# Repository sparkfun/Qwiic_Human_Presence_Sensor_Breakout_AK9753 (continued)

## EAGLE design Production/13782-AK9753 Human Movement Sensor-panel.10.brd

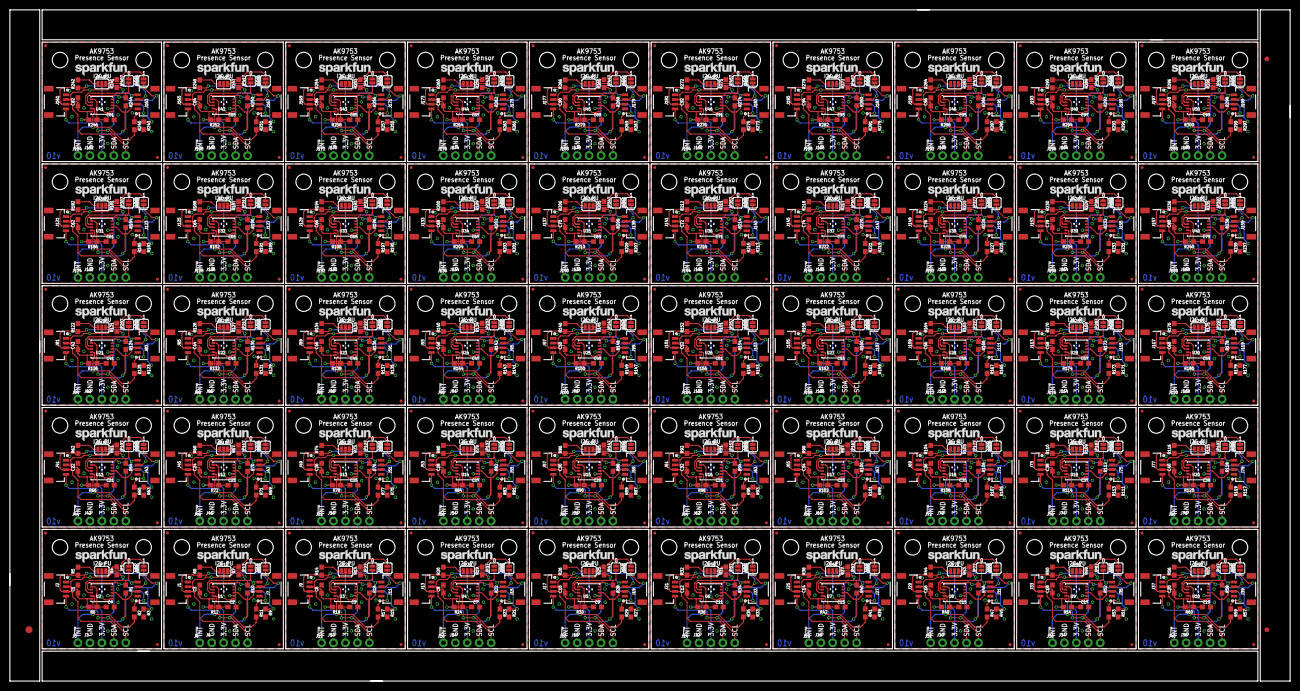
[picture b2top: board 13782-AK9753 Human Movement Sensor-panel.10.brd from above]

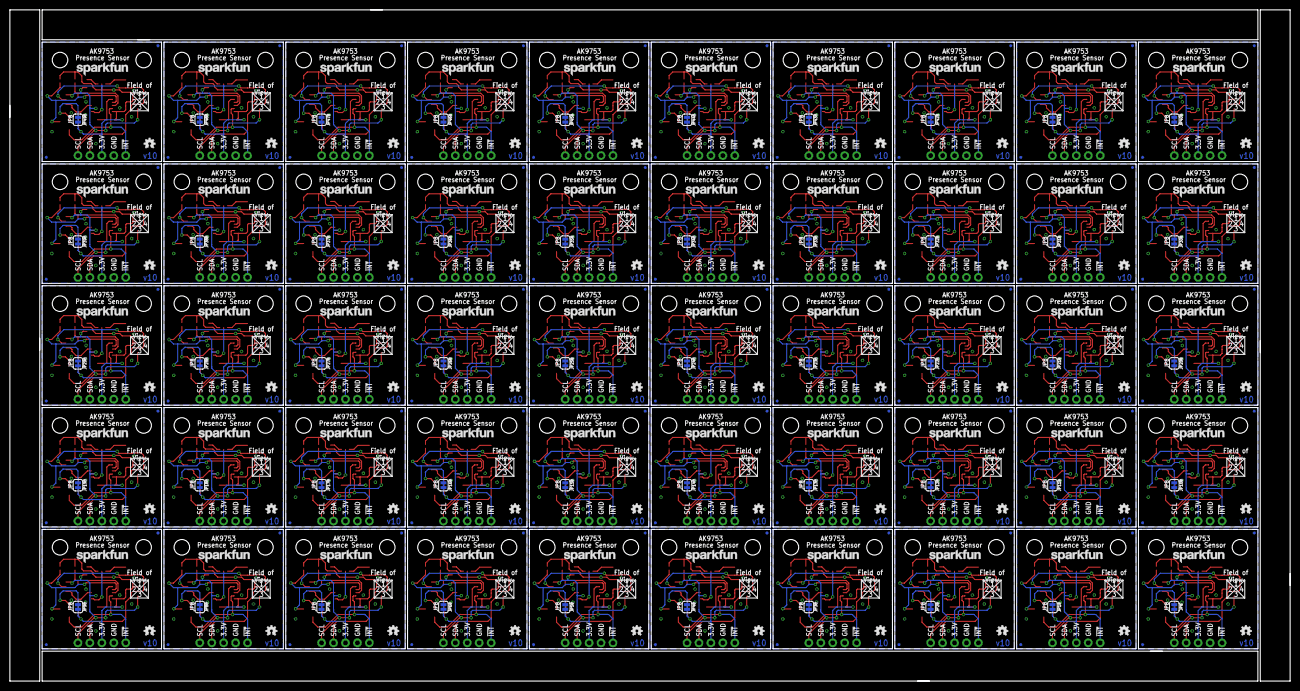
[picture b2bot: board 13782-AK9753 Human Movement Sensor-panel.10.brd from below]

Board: 2 copper layers, 272.3 x 142.7 mm, 1303 parts (250 on the bottom side), 550 nets.

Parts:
C1, C2, C3, C4, C5, C6, C7, C8, C9, C10, C11, C12, C13, C14, C15, C16, C17, C18, C19, C20, C21, C22, C23, C24, C25, C26, C27, C28, C29, C30, C31, C32, C33, C34, C35, C36, C37, C38, C39, C40, C41, C42, C43, C44, C45, C46, C47, C48, C49, C50, C51, C52, C53, C54, C55, C56, C57, C58, C59, C60, C61, C62, C63, C64, C65, C66, C67, C68, C69, C70, C71, C72, C73, C74, C75, C76, C77, C78, C79, C80, C81, C82, C83, C84, C85, C86, C87, C88, C89, C90, C91, C92, C93, C94, C95, C96, C97, C98, C99, C100: 1.0uF; 0603
E$1: FIDUCIAL-1.5X3
E$7, E$8: FIDUCIAL-1X2
J1, J2, J4, J7, J9, J11, J13, J15, J17, J19, J21, J23, J25, J27, J29, J31, J33, J35, J37, J39, J41, J43, J45, J47, J49, J51, J53, J55, J57, J59, J61, J63, J65, J67, J69, J71, J73, J75, J77, J79, J81, J83, J85, J87, J89, J91, J93, J95, J97, J99, J101, J103, J105, J107, J109, J111, J113, J115, J117, J119, J121, J123, J125, J127, J129, J131, J133, J135, J137, J139, J141, J143, J145, J147, J149, J151, J153, J155, J157, J159, J161, J163, J165, J167, J169, J171, J173, J175, J177, J179, J181, J183, J185, J187, J189, J191, J193, J195, J197, J199: 1X04_1MM_RA
J3, J6, J10, J14, J18, J22, J26, J30, J34, J38, J42, J46, J50, J54, J58, J62, J66, J70, J74, J78, J82, J86, J90, J94, J98, J102, J106, J110, J114, J118, J122, J126, J130, J134, J138, J142, J146, J150, J154, J158, J162, J166, J170, J174, J178, J182, J186, J190, J194, J198: PTH; 1X04_NO_SILK
J5, J8, J12, J16, J20, J24, J28, J32, J36, J40, J44, J48, J52, J56, J60, J64, J68, J72, J76, J80, J84, J88, J92, J96, J100, J104, J108, J112, J116, J120, J124, J128, J132, J136, J140, J144, J148, J152, J156, J160, J164, J168, J172, J176, J180, J184, J188, J192, J196, J200: 1X01_NO_SILK
JP1, JP5, JP16, JP17, JP26, JP27, JP36, JP37, JP46, JP47, JP56, JP57, JP66, JP67, JP76, JP77, JP86, JP87, JP96, JP97, JP106, JP107, JP116, JP117, JP126, JP127, JP136, JP137, JP146, JP147, JP156, JP157, JP166, JP167, JP176, JP177, JP186, JP187, JP196, JP197, JP206, JP207, JP216, JP217, JP226, JP227, JP236, JP237, JP246, JP247, JP256, JP257, JP266, JP267, JP276, JP277, JP286, JP287, JP296, JP297, JP306, JP307, JP316, JP317, JP326, JP327, JP336, JP337, JP346, JP347, JP356, JP357, JP366, JP367, JP376, JP377, JP386, JP387, JP396, JP397, JP406, JP407, JP416, JP417, JP426, JP427, JP436, JP437, JP446, JP447, JP456, JP457, JP466, JP467, JP476, JP477, JP486, JP487, JP496, JP497: SMT-JUMPER_2_NO_SILK
JP2, JP6, JP9, JP10, JP13, JP14, JP19, JP20, JP23, JP24, JP29, JP30, JP33, JP34, JP39, JP40, JP43, JP44, JP49, JP50, JP53, JP54, JP59, JP60, JP63, JP64, JP69, JP70, JP73, JP74, JP79, JP80, JP83, JP84, JP89, JP90, JP93, JP94, JP99, JP100, JP103, JP104, JP109, JP110, JP113, JP114, JP119, JP120, JP123, JP124, JP129, JP130, JP133, JP134, JP139, JP140, JP143, JP144, JP149, JP150, JP153, JP154, JP159, JP160, JP163, JP164, JP169, JP170, JP173, JP174, JP179, JP180, JP183, JP184, JP189, JP190, JP193, JP194, JP199, JP200, JP203, JP204, JP209, JP210, JP213, JP214, JP219, JP220, JP223, JP224, JP229, JP230, JP233, JP234, JP239, JP240, JP243, JP244, JP249, JP250, JP253, JP254, JP259, JP260, JP263, JP264, JP269, JP270, JP273, JP274, JP279, JP280, JP283, JP284, JP289, JP290, JP293, JP294, JP299, JP300, JP303, JP304, JP309, JP310, JP313, JP314, JP319, JP320, JP323, JP324, JP329, JP330, JP333, JP334, JP339, JP340, JP343, JP344, JP349, JP350, JP353, JP354, JP359, JP360, JP363, JP364, JP369, JP370, JP373, JP374, JP379, JP380, JP383, JP384, JP389, JP390, JP393, JP394, JP399, JP400, JP403, JP404, JP409, JP410, JP413, JP414, JP419, JP420, JP423, JP424, JP429, JP430, JP433, JP434, JP439, JP440, JP443, JP444, JP449, JP450, JP453, JP454, JP459, JP460, JP463, JP464, JP469, JP470, JP473, JP474, JP479, JP480, JP483, JP484, JP489, JP490, JP493, JP494, JP499, JP500: FIDUCIALUFIDUCIAL; MICRO-FIDUCIAL
JP3, JP4, JP11, JP12, JP21, JP22, JP31, JP32, JP41, JP42, JP51, JP52, JP61, JP62, JP71, JP72, JP81, JP82, JP91, JP92, JP101, JP102, JP111, JP112, JP121, JP122, JP131, JP132, JP141, JP142, JP151, JP152, JP161, JP162, JP171, JP172, JP181, JP182, JP191, JP192, JP201, JP202, JP211, JP212, JP221, JP222, JP231, JP232, JP241, JP242, JP251, JP252, JP261, JP262, JP271, JP272, JP281, JP282, JP291, JP292, JP301, JP302, JP311, JP312, JP321, JP322, JP331, JP332, JP341, JP342, JP351, JP352, JP361, JP362, JP371, JP372, JP381, JP382, JP391, JP392, JP401, JP402, JP411, JP412, JP421, JP422, JP431, JP432, JP441, JP442, JP451, JP452, JP461, JP462, JP471, JP472, JP481, JP482, JP491, JP492: STAND-OFF
JP7, JP15, JP25, JP35, JP45, JP55, JP65, JP75, JP85, JP95, JP105, JP115, JP125, JP135, JP145, JP155, JP165, JP175, JP185, JP195, JP205, JP215, JP225, JP235, JP245, JP255, JP265, JP275, JP285, JP295, JP305, JP315, JP325, JP335, JP345, JP355, JP365, JP375, JP385, JP395, JP405, JP415, JP425, JP435, JP445, JP455, JP465, JP475, JP485, JP495: SMT-JUMPER_3_2-NC_PASTE_SILK
JP8, JP18, JP28, JP38, JP48, JP58, JP68, JP78, JP88, JP98, JP108, JP118, JP128, JP138, JP148, JP158, JP168, JP178, JP188, JP198, JP208, JP218, JP228, JP238, JP248, JP258, JP268, JP278, JP288, JP298, JP308, JP318, JP328, JP338, JP348, JP358, JP368, JP378, JP388, JP398, JP408, JP418, JP428, JP438, JP448, JP458, JP468, JP478, JP488, JP498: SMT-JUMPER_2_NC_TRACE_SILK
LOGO1, LOGO3, LOGO5, LOGO7, LOGO9, LOGO11, LOGO13, LOGO15, LOGO17, LOGO19, LOGO21, LOGO23, LOGO25, LOGO27, LOGO29, LOGO31, LOGO33, LOGO35, LOGO37, LOGO39, LOGO41, LOGO43, LOGO45, LOGO47, LOGO49, LOGO51, LOGO53, LOGO55, LOGO57, LOGO59, LOGO61, LOGO63, LOGO65, LOGO67, LOGO69, LOGO71, LOGO73, LOGO75, LOGO77, LOGO79, LOGO81, LOGO83, LOGO85, LOGO87, LOGO89, LOGO91, LOGO93, LOGO95, LOGO97, LOGO99: OSHW-LOGOMINI; OSHW-LOGO-MINI
LOGO2, LOGO4, LOGO6, LOGO8, LOGO10, LOGO12, LOGO14, LOGO16, LOGO18, LOGO20, LOGO22, LOGO24, LOGO26, LOGO28, LOGO30, LOGO32, LOGO34, LOGO36, LOGO38, LOGO40, LOGO42, LOGO44, LOGO46, LOGO48, LOGO50, LOGO52, LOGO54, LOGO56, LOGO58, LOGO60, LOGO62, LOGO64, LOGO66, LOGO68, LOGO70, LOGO72, LOGO74, LOGO76, LOGO78, LOGO80, LOGO82, LOGO84, LOGO86, LOGO88, LOGO90, LOGO92, LOGO94, LOGO96, LOGO98, LOGO100: SFE_LOGO_NAME.1_INCH; SFE_LOGO_NAME_.1
R1, R2, R3, R9, R10, R11, R15, R16, R17, R21, R22, R23, R27, R28, R29, R33, R34, R35, R39, R40, R41, R45, R46, R47, R51, R52, R53, R57, R58, R59, R63, R64, R65, R69, R70, R71, R75, R76, R77, R81, R82, R83, R87, R88, R89, R93, R94, R95, R99, R100, R101, R105, R106, R107, R111, R112, R113, R117, R118, R119, R123, R124, R125, R129, R130, R131, R135, R136, R137, R141, R142, R143, R147, R148, R149, R153, R154, R155, R159, R160, R161, R165, R166, R167, R171, R172, R173, R177, R178, R179, R183, R184, R185, R189, R190, R191, R195, R196, R197, R201, R202, R203, R207, R208, R209, R213, R214, R215, R219, R220, R221, R225, R226, R227, R231, R232, R233, R237, R238, R239, R243, R244, R245, R249, R250, R251, R255, R256, R257, R261, R262, R263, R267, R268, R269, R273, R274, R275, R279, R280, R281, R285, R286, R287, R291, R292, R293, R297, R298, R299: 10k; 0603
R4, R5, R7, R8, R13, R14, R19, R20, R25, R26, R31, R32, R37, R38, R43, R44, R49, R50, R55, R56, R61, R62, R67, R68, R73, R74, R79, R80, R85, R86, R91, R92, R97, R98, R103, R104, R109, R110, R115, R116, R121, R122, R127, R128, R133, R134, R139, R140, R145, R146, R151, R152, R157, R158, R163, R164, R169, R170, R175, R176, R181, R182, R187, R188, R193, R194, R199, R200, R205, R206, R211, R212, R217, R218, R223, R224, R229, R230, R235, R236, R241, R242, R247, R248, R253, R254, R259, R260, R265, R266, R271, R272, R277, R278, R283, R284, R289, R290, R295, R296: 4.7k; 0603
R6, R12, R18, R24, R30, R36, R42, R48, R54, R60, R66, R72, R78, R84, R90, R96, R102, R108, R114, R120, R126, R132, R138, R144, R150, R156, R162, R168, R174, R180, R186, R192, R198, R204, R210, R216, R222, R228, R234, R240, R246, R252, R258, R264, R270, R276, R282, R288, R294, R300: 330; 0603
U1, U2, U3, U4, U5, U6, U7, U8, U9, U10, U11, U12, U13, U14, U15, U16, U17, U18, U19, U20, U21, U22, U23, U24, U25, U26, U27, U28, U29, U30, U31, U32, U33, U34, U35, U36, U37, U38, U39, U40, U41, U42, U43, U44, U45, U46, U47, U48, U49, U50: AK9753; SON10
U$1, U$2, U$3, U$4, U$5, U$6, U$7, U$8, U$9, U$10, U$11, U$12, U$13, U$14, U$15, U$16, U$17, U$18, U$19, U$20, U$21, U$22, U$23, U$24, U$25, U$26, U$27, U$28, U$29, U$30, U$31, U$32, U$33, U$34, U$35, U$36, U$37, U$38, U$39, U$40, U$41, U$42, U$43, U$44, U$45, U$46, U$47, U$48, U$49, U$50: SFE_LOGO_NAME_.1

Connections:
3.3V: C1.1, J2.2, J3.2, J4.2, JP1.2, JP5.2, JP7.2, JP8.2, R6.2, U2.3, U2.6
3.3V1: C3.1, J1.2, J6.2, J7.2, JP15.2, JP16.2, JP17.2, JP18.2, R12.2, U1.3, U1.6
3.3V2: C6.1, J9.2, J10.2, J11.2, JP25.2, JP26.2, JP27.2, JP28.2, R18.2, U3.3, U3.6
3.3V3: C8.1, J13.2, J14.2, J15.2, JP35.2, JP36.2, JP37.2, JP38.2, R24.2, U4.3, U4.6
3.3V4: C10.1, J17.2, J18.2, J19.2, JP45.2, JP46.2, JP47.2, JP48.2, R30.2, U5.3, U5.6
3.3V5: C12.1, J21.2, J22.2, J23.2, JP55.2, JP56.2, JP57.2, JP58.2, R36.2, U6.3, U6.6
3.3V6: C14.1, J25.2, J26.2, J27.2, JP65.2, JP66.2, JP67.2, JP68.2, R42.2, U7.3, U7.6
3.3V7: C16.1, J29.2, J30.2, J31.2, JP75.2, JP76.2, JP77.2, JP78.2, R48.2, U8.3, U8.6
3.3V8: C18.1, J33.2, J34.2, J35.2, JP85.2, JP86.2, JP87.2, JP88.2, R54.2, U9.3, U9.6
3.3V9: C20.1, J37.2, J38.2, J39.2, JP95.2, JP96.2, JP97.2, JP98.2, R60.2, U10.3, U10.6
3.3V10: C22.1, J41.2, J42.2, J43.2, JP105.2, JP106.2, JP107.2, JP108.2, R66.2, U11.3, U11.6
3.3V11: C24.1, J45.2, J46.2, J47.2, JP115.2, JP116.2, JP117.2, JP118.2, R72.2, U12.3, U12.6
3.3V12: C26.1, J49.2, J50.2, J51.2, JP125.2, JP126.2, JP127.2, JP128.2, R78.2, U13.3, U13.6
3.3V13: C28.1, J53.2, J54.2, J55.2, JP135.2, JP136.2, JP137.2, JP138.2, R84.2, U14.3, U14.6
3.3V14: C30.1, J57.2, J58.2, J59.2, JP145.2, JP146.2, JP147.2, JP148.2, R90.2, U15.3, U15.6
3.3V15: C32.1, J61.2, J62.2, J63.2, JP155.2, JP156.2, JP157.2, JP158.2, R96.2, U16.3, U16.6
3.3V16: C34.1, J65.2, J66.2, J67.2, JP165.2, JP166.2, JP167.2, JP168.2, R102.2, U17.3, U17.6
3.3V17: C36.1, J69.2, J70.2, J71.2, JP175.2, JP176.2, JP177.2, JP178.2, R108.2, U18.3, U18.6
3.3V18: C38.1, J73.2, J74.2, J75.2, JP185.2, JP186.2, JP187.2, JP188.2, R114.2, U19.3, U19.6
3.3V19: C40.1, J77.2, J78.2, J79.2, JP195.2, JP196.2, JP197.2, JP198.2, R120.2, U20.3, U20.6
3.3V20: C42.1, J81.2, J82.2, J83.2, JP205.2, JP206.2, JP207.2, JP208.2, R126.2, U21.3, U21.6
3.3V21: C44.1, J85.2, J86.2, J87.2, JP215.2, JP216.2, JP217.2, JP218.2, R132.2, U22.3, U22.6
3.3V22: C46.1, J89.2, J90.2, J91.2, JP225.2, JP226.2, JP227.2, JP228.2, R138.2, U23.3, U23.6
3.3V23: C48.1, J93.2, J94.2, J95.2, JP235.2, JP236.2, JP237.2, JP238.2, R144.2, U24.3, U24.6
3.3V24: C50.1, J97.2, J98.2, J99.2, JP245.2, JP246.2, JP247.2, JP248.2, R150.2, U25.3, U25.6
3.3V25: C52.1, J101.2, J102.2, J103.2, JP255.2, JP256.2, JP257.2, JP258.2, R156.2, U26.3, U26.6
3.3V26: C54.1, J105.2, J106.2, J107.2, JP265.2, JP266.2, JP267.2, JP268.2, R162.2, U27.3, U27.6
3.3V27: C56.1, J109.2, J110.2, J111.2, JP275.2, JP276.2, JP277.2, JP278.2, R168.2, U28.3, U28.6
3.3V28: C58.1, J113.2, J114.2, J115.2, JP285.2, JP286.2, JP287.2, JP288.2, R174.2, U29.3, U29.6
3.3V29: C60.1, J117.2, J118.2, J119.2, JP295.2, JP296.2, JP297.2, JP298.2, R180.2, U30.3, U30.6
3.3V30: C62.1, J121.2, J122.2, J123.2, JP305.2, JP306.2, JP307.2, JP308.2, R186.2, U31.3, U31.6
3.3V31: C64.1, J125.2, J126.2, J127.2, JP315.2, JP316.2, JP317.2, JP318.2, R192.2, U32.3, U32.6
3.3V32: C66.1, J129.2, J130.2, J131.2, JP325.2, JP326.2, JP327.2, JP328.2, R198.2, U33.3, U33.6
3.3V33: C68.1, J133.2, J134.2, J135.2, JP335.2, JP336.2, JP337.2, JP338.2, R204.2, U34.3, U34.6
3.3V34: C70.1, J137.2, J138.2, J139.2, JP345.2, JP346.2, JP347.2, JP348.2, R210.2, U35.3, U35.6
3.3V35: C72.1, J141.2, J142.2, J143.2, JP355.2, JP356.2, JP357.2, JP358.2, R216.2, U36.3, U36.6
3.3V36: C74.1, J145.2, J146.2, J147.2, JP365.2, JP366.2, JP367.2, JP368.2, R222.2, U37.3, U37.6
3.3V37: C76.1, J149.2, J150.2, J151.2, JP375.2, JP376.2, JP377.2, JP378.2, R228.2, U38.3, U38.6
3.3V38: C78.1, J153.2, J154.2, J155.2, JP385.2, JP386.2, JP387.2, JP388.2, R234.2, U39.3, U39.6
3.3V39: C80.1, J157.2, J158.2, J159.2, JP395.2, JP396.2, JP397.2, JP398.2, R240.2, U40.3, U40.6
3.3V40: C82.1, J161.2, J162.2, J163.2, JP405.2, JP406.2, JP407.2, JP408.2, R246.2, U41.3, U41.6
3.3V41: C84.1, J165.2, J166.2, J167.2, JP415.2, JP416.2, JP417.2, JP418.2, R252.2, U42.3, U42.6
3.3V42: C86.1, J169.2, J170.2, J171.2, JP425.2, JP426.2, JP427.2, JP428.2, R258.2, U43.3, U43.6
3.3V43: C88.1, J173.2, J174.2, J175.2, JP435.2, JP436.2, JP437.2, JP438.2, R264.2, U44.3, U44.6
3.3V44: C90.1, J177.2, J178.2, J179.2, JP445.2, JP446.2, JP447.2, JP448.2, R270.2, U45.3, U45.6
3.3V45: C92.1, J181.2, J182.2, J183.2, JP455.2, JP456.2, JP457.2, JP458.2, R276.2, U46.3, U46.6
3.3V46: C94.1, J185.2, J186.2, J187.2, JP465.2, JP466.2, JP467.2, JP468.2, R282.2, U47.3, U47.6
3.3V47: C96.1, J189.2, J190.2, J191.2, JP475.2, JP476.2, JP477.2, JP478.2, R288.2, U48.3, U48.6
3.3V48: C98.1, J193.2, J194.2, J195.2, JP485.2, JP486.2, JP487.2, JP488.2, R294.2, U49.3, U49.6
3.3V49: C100.1, J197.2, J198.2, J199.2, JP495.2, JP496.2, JP497.2, JP498.2, R300.2, U50.3, U50.6
!INT: J5.1, R2.2, U2.7
!INT1: J8.1, R11.2, U1.7
!INT2: J12.1, R17.2, U3.7
!INT3: J16.1, R23.2, U4.7
!INT4: J20.1, R29.2, U5.7
!INT5: J24.1, R35.2, U6.7
!INT6: J28.1, R41.2, U7.7
!INT7: J32.1, R47.2, U8.7
!INT8: J36.1, R53.2, U9.7
!INT9: J40.1, R59.2, U10.7
!INT10: J44.1, R65.2, U11.7
!INT11: J48.1, R71.2, U12.7
!INT12: J52.1, R77.2, U13.7
!INT13: J56.1, R83.2, U14.7
!INT14: J60.1, R89.2, U15.7
!INT15: J64.1, R95.2, U16.7
!INT16: J68.1, R101.2, U17.7
!INT17: J72.1, R107.2, U18.7
!INT18: J76.1, R113.2, U19.7
!INT19: J80.1, R119.2, U20.7
!INT20: J84.1, R125.2, U21.7
!INT21: J88.1, R131.2, U22.7
!INT22: J92.1, R137.2, U23.7
!INT23: J96.1, R143.2, U24.7
!INT24: J100.1, R149.2, U25.7
!INT25: J104.1, R155.2, U26.7
!INT26: J108.1, R161.2, U27.7
!INT27: J112.1, R167.2, U28.7
!INT28: J116.1, R173.2, U29.7
!INT29: J120.1, R179.2, U30.7
!INT30: J124.1, R185.2, U31.7
!INT31: J128.1, R191.2, U32.7
!INT32: J132.1, R197.2, U33.7
!INT33: J136.1, R203.2, U34.7
!INT34: J140.1, R209.2, U35.7
!INT35: J144.1, R215.2, U36.7
!INT36: J148.1, R221.2, U37.7
!INT37: J152.1, R227.2, U38.7
!INT38: J156.1, R233.2, U39.7
!INT39: J160.1, R239.2, U40.7
!INT40: J164.1, R245.2, U41.7
!INT41: J168.1, R251.2, U42.7
!INT42: J172.1, R257.2, U43.7
!INT43: J176.1, R263.2, U44.7
!INT44: J180.1, R269.2, U45.7
!INT45: J184.1, R275.2, U46.7
!INT46: J188.1, R281.2, U47.7
!INT47: J192.1, R287.2, U48.7
!INT48: J196.1, R293.2, U49.7
!INT49: J200.1, R299.2, U50.7
ADR0: JP1.1, R3.1, U2.9
ADR1: JP5.1, R1.1, U2.8
ADR2: JP16.1, R9.1, U1.9
ADR3: JP17.1, R10.1, U1.8
ADR4: JP26.1, R15.1, U3.9
ADR5: JP27.1, R16.1, U3.8
ADR6: JP36.1, R21.1, U4.9
ADR7: JP37.1, R22.1, U4.8
ADR8: JP46.1, R27.1, U5.9
ADR9: JP47.1, R28.1, U5.8
ADR10: JP56.1, R33.1, U6.9
ADR11: JP57.1, R34.1, U6.8
ADR12: JP66.1, R39.1, U7.9
ADR13: JP67.1, R40.1, U7.8
ADR14: JP76.1, R45.1, U8.9
ADR15: JP77.1, R46.1, U8.8
ADR16: JP86.1, R51.1, U9.9
ADR17: JP87.1, R52.1, U9.8
ADR18: JP96.1, R57.1, U10.9
ADR19: JP97.1, R58.1, U10.8
ADR20: JP106.1, R63.1, U11.9
ADR21: JP107.1, R64.1, U11.8
ADR22: JP116.1, R69.1, U12.9
ADR23: JP117.1, R70.1, U12.8
ADR24: JP126.1, R75.1, U13.9
ADR25: JP127.1, R76.1, U13.8
ADR26: JP136.1, R81.1, U14.9
ADR27: JP137.1, R82.1, U14.8
ADR28: JP146.1, R87.1, U15.9
ADR29: JP147.1, R88.1, U15.8
ADR30: JP156.1, R93.1, U16.9
ADR31: JP157.1, R94.1, U16.8
ADR32: JP166.1, R99.1, U17.9
ADR33: JP167.1, R100.1, U17.8
ADR34: JP176.1, R105.1, U18.9
ADR35: JP177.1, R106.1, U18.8
ADR36: JP186.1, R111.1, U19.9
ADR37: JP187.1, R112.1, U19.8
ADR38: JP196.1, R117.1, U20.9
ADR39: JP197.1, R118.1, U20.8
ADR40: JP206.1, R123.1, U21.9
ADR41: JP207.1, R124.1, U21.8
ADR42: JP216.1, R129.1, U22.9
ADR43: JP217.1, R130.1, U22.8
ADR44: JP226.1, R135.1, U23.9
ADR45: JP227.1, R136.1, U23.8
ADR46: JP236.1, R141.1, U24.9
ADR47: JP237.1, R142.1, U24.8
ADR48: JP246.1, R147.1, U25.9
ADR49: JP247.1, R148.1, U25.8
ADR50: JP256.1, R153.1, U26.9
ADR51: JP257.1, R154.1, U26.8
ADR52: JP266.1, R159.1, U27.9
ADR53: JP267.1, R160.1, U27.8
ADR54: JP276.1, R165.1, U28.9
ADR55: JP277.1, R166.1, U28.8
ADR56: JP286.1, R171.1, U29.9
ADR57: JP287.1, R172.1, U29.8
ADR58: JP296.1, R177.1, U30.9
ADR59: JP297.1, R178.1, U30.8
ADR60: JP306.1, R183.1, U31.9
ADR61: JP307.1, R184.1, U31.8
ADR62: JP316.1, R189.1, U32.9
ADR63: JP317.1, R190.1, U32.8
ADR64: JP326.1, R195.1, U33.9
ADR65: JP327.1, R196.1, U33.8
ADR66: JP336.1, R201.1, U34.9
ADR67: JP337.1, R202.1, U34.8
ADR68: JP346.1, R207.1, U35.9
ADR69: JP347.1, R208.1, U35.8
ADR70: JP356.1, R213.1, U36.9
ADR71: JP357.1, R214.1, U36.8
ADR72: JP366.1, R219.1, U37.9
ADR73: JP367.1, R220.1, U37.8
ADR74: JP376.1, R225.1, U38.9
ADR75: JP377.1, R226.1, U38.8
ADR76: JP386.1, R231.1, U39.9
ADR77: JP387.1, R232.1, U39.8
ADR78: JP396.1, R237.1, U40.9
ADR79: JP397.1, R238.1, U40.8
ADR80: JP406.1, R243.1, U41.9
ADR81: JP407.1, R244.1, U41.8
ADR82: JP416.1, R249.1, U42.9
ADR83: JP417.1, R250.1, U42.8
ADR84: JP426.1, R255.1, U43.9
ADR85: JP427.1, R256.1, U43.8
ADR86: JP436.1, R261.1, U44.9
ADR87: JP437.1, R262.1, U44.8
ADR88: JP446.1, R267.1, U45.9
ADR89: JP447.1, R268.1, U45.8
ADR90: JP456.1, R273.1, U46.9
ADR91: JP457.1, R274.1, U46.8
ADR92: JP466.1, R279.1, U47.9
ADR93: JP467.1, R280.1, U47.8
ADR94: JP476.1, R285.1, U48.9
ADR95: JP477.1, R286.1, U48.8
ADR96: JP486.1, R291.1, U49.9
ADR97: JP487.1, R292.1, U49.8
ADR98: JP496.1, R297.1, U50.9
ADR99: JP497.1, R298.1, U50.8
GND: C1.2, C4.2, J2.1, J3.1, J4.1, R1.2, R3.2, U2.1, U2.2
GND1: C2.2, C3.2, J1.1, J6.1, J7.1, R9.2, R10.2, U1.1, U1.2
GND2: C5.2, C6.2, J9.1, J10.1, J11.1, R15.2, R16.2, U3.1, U3.2
GND3: C7.2, C8.2, J13.1, J14.1, J15.1, R21.2, R22.2, U4.1, U4.2
GND4: C9.2, C10.2, J17.1, J18.1, J19.1, R27.2, R28.2, U5.1, U5.2
GND5: C11.2, C12.2, J21.1, J22.1, J23.1, R33.2, R34.2, U6.1, U6.2
GND6: C13.2, C14.2, J25.1, J26.1, J27.1, R39.2, R40.2, U7.1, U7.2
GND7: C15.2, C16.2, J29.1, J30.1, J31.1, R45.2, R46.2, U8.1, U8.2
GND8: C17.2, C18.2, J33.1, J34.1, J35.1, R51.2, R52.2, U9.1, U9.2
GND9: C19.2, C20.2, J37.1, J38.1, J39.1, R57.2, R58.2, U10.1, U10.2
GND10: C21.2, C22.2, J41.1, J42.1, J43.1, R63.2, R64.2, U11.1, U11.2
GND11: C23.2, C24.2, J45.1, J46.1, J47.1, R69.2, R70.2, U12.1, U12.2
GND12: C25.2, C26.2, J49.1, J50.1, J51.1, R75.2, R76.2, U13.1, U13.2
GND13: C27.2, C28.2, J53.1, J54.1, J55.1, R81.2, R82.2, U14.1, U14.2
GND14: C29.2, C30.2, J57.1, J58.1, J59.1, R87.2, R88.2, U15.1, U15.2
GND15: C31.2, C32.2, J61.1, J62.1, J63.1, R93.2, R94.2, U16.1, U16.2
GND16: C33.2, C34.2, J65.1, J66.1, J67.1, R99.2, R100.2, U17.1, U17.2
GND17: C35.2, C36.2, J69.1, J70.1, J71.1, R105.2, R106.2, U18.1, U18.2
GND18: C37.2, C38.2, J73.1, J74.1, J75.1, R111.2, R112.2, U19.1, U19.2
GND19: C39.2, C40.2, J77.1, J78.1, J79.1, R117.2, R118.2, U20.1, U20.2
GND20: C41.2, C42.2, J81.1, J82.1, J83.1, R123.2, R124.2, U21.1, U21.2
GND21: C43.2, C44.2, J85.1, J86.1, J87.1, R129.2, R130.2, U22.1, U22.2
GND22: C45.2, C46.2, J89.1, J90.1, J91.1, R135.2, R136.2, U23.1, U23.2
GND23: C47.2, C48.2, J93.1, J94.1, J95.1, R141.2, R142.2, U24.1, U24.2
GND24: C49.2, C50.2, J97.1, J98.1, J99.1, R147.2, R148.2, U25.1, U25.2
GND25: C51.2, C52.2, J101.1, J102.1, J103.1, R153.2, R154.2, U26.1, U26.2
GND26: C53.2, C54.2, J105.1, J106.1, J107.1, R159.2, R160.2, U27.1, U27.2
GND27: C55.2, C56.2, J109.1, J110.1, J111.1, R165.2, R166.2, U28.1, U28.2
GND28: C57.2, C58.2, J113.1, J114.1, J115.1, R171.2, R172.2, U29.1, U29.2
GND29: C59.2, C60.2, J117.1, J118.1, J119.1, R177.2, R178.2, U30.1, U30.2
GND30: C61.2, C62.2, J121.1, J122.1, J123.1, R183.2, R184.2, U31.1, U31.2
GND31: C63.2, C64.2, J125.1, J126.1, J127.1, R189.2, R190.2, U32.1, U32.2
GND32: C65.2, C66.2, J129.1, J130.1, J131.1, R195.2, R196.2, U33.1, U33.2
GND33: C67.2, C68.2, J133.1, J134.1, J135.1, R201.2, R202.2, U34.1, U34.2
GND34: C69.2, C70.2, J137.1, J138.1, J139.1, R207.2, R208.2, U35.1, U35.2
GND35: C71.2, C72.2, J141.1, J142.1, J143.1, R213.2, R214.2, U36.1, U36.2
GND36: C73.2, C74.2, J145.1, J146.1, J147.1, R219.2, R220.2, U37.1, U37.2
GND37: C75.2, C76.2, J149.1, J150.1, J151.1, R225.2, R226.2, U38.1, U38.2
GND38: C77.2, C78.2, J153.1, J154.1, J155.1, R231.2, R232.2, U39.1, U39.2
GND39: C79.2, C80.2, J157.1, J158.1, J159.1, R237.2, R238.2, U40.1, U40.2
GND40: C81.2, C82.2, J161.1, J162.1, J163.1, R243.2, R244.2, U41.1, U41.2
GND41: C83.2, C84.2, J165.1, J166.1, J167.1, R249.2, R250.2, U42.1, U42.2
GND42: C85.2, C86.2, J169.1, J170.1, J171.1, R255.2, R256.2, U43.1, U43.2
GND43: C87.2, C88.2, J173.1, J174.1, J175.1, R261.2, R262.2, U44.1, U44.2
GND44: C89.2, C90.2, J177.1, J178.1, J179.1, R267.2, R268.2, U45.1, U45.2
GND45: C91.2, C92.2, J181.1, J182.1, J183.1, R273.2, R274.2, U46.1, U46.2
GND46: C93.2, C94.2, J185.1, J186.1, J187.1, R279.2, R280.2, U47.1, U47.2
GND47: C95.2, C96.2, J189.1, J190.1, J191.1, R285.2, R286.2, U48.1, U48.2
GND48: C97.2, C98.2, J193.1, J194.1, J195.1, R291.2, R292.2, U49.1, U49.2
GND49: C99.2, C100.2, J197.1, J198.1, J199.1, R297.2, R298.2, U50.1, U50.2
unnamed: JP7.1, R5.2
unnamed: JP7.3, R4.2
unnamed: JP8.1, R2.1
unnamed: JP15.1, R8.2
unnamed: JP15.3, R7.2
unnamed: JP18.1, R11.1
unnamed: JP25.1, R14.2
unnamed: JP25.3, R13.2
unnamed: JP28.1, R17.1
unnamed: JP35.1, R20.2
unnamed: JP35.3, R19.2
unnamed: JP38.1, R23.1
unnamed: JP45.1, R26.2
unnamed: JP45.3, R25.2
unnamed: JP48.1, R29.1
unnamed: JP55.1, R32.2
unnamed: JP55.3, R31.2
unnamed: JP58.1, R35.1
unnamed: JP65.1, R38.2
unnamed: JP65.3, R37.2
unnamed: JP68.1, R41.1
unnamed: JP75.1, R44.2
unnamed: JP75.3, R43.2
unnamed: JP78.1, R47.1
unnamed: JP85.1, R50.2
unnamed: JP85.3, R49.2
unnamed: JP88.1, R53.1
unnamed: JP95.1, R56.2
unnamed: JP95.3, R55.2
unnamed: JP98.1, R59.1
unnamed: JP105.1, R62.2
unnamed: JP105.3, R61.2
unnamed: JP108.1, R65.1
unnamed: JP115.1, R68.2
unnamed: JP115.3, R67.2
unnamed: JP118.1, R71.1
unnamed: JP125.1, R74.2
unnamed: JP125.3, R73.2
unnamed: JP128.1, R77.1
unnamed: JP135.1, R80.2
unnamed: JP135.3, R79.2
unnamed: JP138.1, R83.1
unnamed: JP145.1, R86.2
unnamed: JP145.3, R85.2
unnamed: JP148.1, R89.1
unnamed: JP155.1, R92.2
unnamed: JP155.3, R91.2
unnamed: JP158.1, R95.1
unnamed: JP165.1, R98.2
unnamed: JP165.3, R97.2
unnamed: JP168.1, R101.1
unnamed: JP175.1, R104.2
unnamed: JP175.3, R103.2
unnamed: JP178.1, R107.1
unnamed: JP185.1, R110.2
unnamed: JP185.3, R109.2
unnamed: JP188.1, R113.1
unnamed: JP195.1, R116.2
unnamed: JP195.3, R115.2
unnamed: JP198.1, R119.1
unnamed: JP205.1, R122.2
unnamed: JP205.3, R121.2
unnamed: JP208.1, R125.1
unnamed: JP215.1, R128.2
unnamed: JP215.3, R127.2
unnamed: JP218.1, R131.1
unnamed: JP225.1, R134.2
unnamed: JP225.3, R133.2
unnamed: JP228.1, R137.1
unnamed: JP235.1, R140.2
unnamed: JP235.3, R139.2
unnamed: JP238.1, R143.1
unnamed: JP245.1, R146.2
unnamed: JP245.3, R145.2
unnamed: JP248.1, R149.1
unnamed: JP255.1, R152.2
unnamed: JP255.3, R151.2
unnamed: JP258.1, R155.1
unnamed: JP265.1, R158.2
unnamed: JP265.3, R157.2
unnamed: JP268.1, R161.1
unnamed: JP275.1, R164.2
unnamed: JP275.3, R163.2
unnamed: JP278.1, R167.1
unnamed: JP285.1, R170.2
unnamed: JP285.3, R169.2
unnamed: JP288.1, R173.1
unnamed: JP295.1, R176.2
unnamed: JP295.3, R175.2
unnamed: JP298.1, R179.1
unnamed: JP305.1, R182.2
unnamed: JP305.3, R181.2
unnamed: JP308.1, R185.1
unnamed: JP315.1, R188.2
unnamed: JP315.3, R187.2
unnamed: JP318.1, R191.1
unnamed: JP325.1, R194.2
unnamed: JP325.3, R193.2
unnamed: JP328.1, R197.1
unnamed: JP335.1, R200.2
unnamed: JP335.3, R199.2
unnamed: JP338.1, R203.1
unnamed: JP345.1, R206.2
unnamed: JP345.3, R205.2
unnamed: JP348.1, R209.1
unnamed: JP355.1, R212.2
unnamed: JP355.3, R211.2
unnamed: JP358.1, R215.1
unnamed: JP365.1, R218.2
unnamed: JP365.3, R217.2
unnamed: JP368.1, R221.1
unnamed: JP375.1, R224.2
unnamed: JP375.3, R223.2
unnamed: JP378.1, R227.1
unnamed: JP385.1, R230.2
unnamed: JP385.3, R229.2
unnamed: JP388.1, R233.1
unnamed: JP395.1, R236.2
unnamed: JP395.3, R235.2
unnamed: JP398.1, R239.1
unnamed: JP405.1, R242.2
unnamed: JP405.3, R241.2
unnamed: JP408.1, R245.1
unnamed: JP415.1, R248.2
unnamed: JP415.3, R247.2
unnamed: JP418.1, R251.1
unnamed: JP425.1, R254.2
unnamed: JP425.3, R253.2
unnamed: JP428.1, R257.1
unnamed: JP435.1, R260.2
unnamed: JP435.3, R259.2
unnamed: JP438.1, R263.1
unnamed: JP445.1, R266.2
unnamed: JP445.3, R265.2
unnamed: JP448.1, R269.1
unnamed: JP455.1, R272.2
unnamed: JP455.3, R271.2
unnamed: JP458.1, R275.1
unnamed: JP465.1, R278.2
unnamed: JP465.3, R277.2
unnamed: JP468.1, R281.1
unnamed: JP475.1, R284.2
unnamed: JP475.3, R283.2
unnamed: JP478.1, R287.1
unnamed: JP485.1, R290.2
unnamed: JP485.3, R289.2
unnamed: JP488.1, R293.1
unnamed: JP495.1, R296.2
unnamed: JP495.3, R295.2
unnamed: JP498.1, R299.1
SCL: J2.4, J3.4, J4.4, R4.1, U2.4
SCL1: J1.4, J6.4, J7.4, R7.1, U1.4
SCL2: J9.4, J10.4, J11.4, R13.1, U3.4
SCL3: J13.4, J14.4, J15.4, R19.1, U4.4
SCL4: J17.4, J18.4, J19.4, R25.1, U5.4
SCL5: J21.4, J22.4, J23.4, R31.1, U6.4
SCL6: J25.4, J26.4, J27.4, R37.1, U7.4
SCL7: J29.4, J30.4, J31.4, R43.1, U8.4
SCL8: J33.4, J34.4, J35.4, R49.1, U9.4
SCL9: J37.4, J38.4, J39.4, R55.1, U10.4
SCL10: J41.4, J42.4, J43.4, R61.1, U11.4
SCL11: J45.4, J46.4, J47.4, R67.1, U12.4
SCL12: J49.4, J50.4, J51.4, R73.1, U13.4
SCL13: J53.4, J54.4, J55.4, R79.1, U14.4
SCL14: J57.4, J58.4, J59.4, R85.1, U15.4
SCL15: J61.4, J62.4, J63.4, R91.1, U16.4
SCL16: J65.4, J66.4, J67.4, R97.1, U17.4
SCL17: J69.4, J70.4, J71.4, R103.1, U18.4
SCL18: J73.4, J74.4, J75.4, R109.1, U19.4
SCL19: J77.4, J78.4, J79.4, R115.1, U20.4
SCL20: J81.4, J82.4, J83.4, R121.1, U21.4
SCL21: J85.4, J86.4, J87.4, R127.1, U22.4
SCL22: J89.4, J90.4, J91.4, R133.1, U23.4
SCL23: J93.4, J94.4, J95.4, R139.1, U24.4
SCL24: J97.4, J98.4, J99.4, R145.1, U25.4
SCL25: J101.4, J102.4, J103.4, R151.1, U26.4
SCL26: J105.4, J106.4, J107.4, R157.1, U27.4
SCL27: J109.4, J110.4, J111.4, R163.1, U28.4
SCL28: J113.4, J114.4, J115.4, R169.1, U29.4
SCL29: J117.4, J118.4, J119.4, R175.1, U30.4
SCL30: J121.4, J122.4, J123.4, R181.1, U31.4
SCL31: J125.4, J126.4, J127.4, R187.1, U32.4
SCL32: J129.4, J130.4, J131.4, R193.1, U33.4
SCL33: J133.4, J134.4, J135.4, R199.1, U34.4
SCL34: J137.4, J138.4, J139.4, R205.1, U35.4
SCL35: J141.4, J142.4, J143.4, R211.1, U36.4
SCL36: J145.4, J146.4, J147.4, R217.1, U37.4
SCL37: J149.4, J150.4, J151.4, R223.1, U38.4
SCL38: J153.4, J154.4, J155.4, R229.1, U39.4
SCL39: J157.4, J158.4, J159.4, R235.1, U40.4
SCL40: J161.4, J162.4, J163.4, R241.1, U41.4
SCL41: J165.4, J166.4, J167.4, R247.1, U42.4
SCL42: J169.4, J170.4, J171.4, R253.1, U43.4
SCL43: J173.4, J174.4, J175.4, R259.1, U44.4
SCL44: J177.4, J178.4, J179.4, R265.1, U45.4
SCL45: J181.4, J182.4, J183.4, R271.1, U46.4
SCL46: J185.4, J186.4, J187.4, R277.1, U47.4
SCL47: J189.4, J190.4, J191.4, R283.1, U48.4
SCL48: J193.4, J194.4, J195.4, R289.1, U49.4
SCL49: J197.4, J198.4, J199.4, R295.1, U50.4
SDA: J2.3, J3.3, J4.3, R5.1, U2.5
SDA1: J1.3, J6.3, J7.3, R8.1, U1.5
SDA2: J9.3, J10.3, J11.3, R14.1, U3.5
SDA3: J13.3, J14.3, J15.3, R20.1, U4.5
SDA4: J17.3, J18.3, J19.3, R26.1, U5.5
SDA5: J21.3, J22.3, J23.3, R32.1, U6.5
SDA6: J25.3, J26.3, J27.3, R38.1, U7.5
SDA7: J29.3, J30.3, J31.3, R44.1, U8.5
SDA8: J33.3, J34.3, J35.3, R50.1, U9.5
SDA9: J37.3, J38.3, J39.3, R56.1, U10.5
SDA10: J41.3, J42.3, J43.3, R62.1, U11.5
SDA11: J45.3, J46.3, J47.3, R68.1, U12.5
SDA12: J49.3, J50.3, J51.3, R74.1, U13.5
SDA13: J53.3, J54.3, J55.3, R80.1, U14.5
SDA14: J57.3, J58.3, J59.3, R86.1, U15.5
SDA15: J61.3, J62.3, J63.3, R92.1, U16.5
SDA16: J65.3, J66.3, J67.3, R98.1, U17.5
SDA17: J69.3, J70.3, J71.3, R104.1, U18.5
SDA18: J73.3, J74.3, J75.3, R110.1, U19.5
SDA19: J77.3, J78.3, J79.3, R116.1, U20.5
SDA20: J81.3, J82.3, J83.3, R122.1, U21.5
SDA21: J85.3, J86.3, J87.3, R128.1, U22.5
SDA22: J89.3, J90.3, J91.3, R134.1, U23.5
SDA23: J93.3, J94.3, J95.3, R140.1, U24.5
SDA24: J97.3, J98.3, J99.3, R146.1, U25.5
SDA25: J101.3, J102.3, J103.3, R152.1, U26.5
SDA26: J105.3, J106.3, J107.3, R158.1, U27.5
SDA27: J109.3, J110.3, J111.3, R164.1, U28.5
SDA28: J113.3, J114.3, J115.3, R170.1, U29.5
SDA29: J117.3, J118.3, J119.3, R176.1, U30.5
SDA30: J121.3, J122.3, J123.3, R182.1, U31.5
SDA31: J125.3, J126.3, J127.3, R188.1, U32.5
SDA32: J129.3, J130.3, J131.3, R194.1, U33.5
SDA33: J133.3, J134.3, J135.3, R200.1, U34.5
SDA34: J137.3, J138.3, J139.3, R206.1, U35.5
SDA35: J141.3, J142.3, J143.3, R212.1, U36.5
SDA36: J145.3, J146.3, J147.3, R218.1, U37.5
SDA37: J149.3, J150.3, J151.3, R224.1, U38.5
SDA38: J153.3, J154.3, J155.3, R230.1, U39.5
SDA39: J157.3, J158.3, J159.3, R236.1, U40.5
SDA40: J161.3, J162.3, J163.3, R242.1, U41.5
SDA41: J165.3, J166.3, J167.3, R248.1, U42.5
SDA42: J169.3, J170.3, J171.3, R254.1, U43.5
SDA43: J173.3, J174.3, J175.3, R260.1, U44.5
SDA44: J177.3, J178.3, J179.3, R266.1, U45.5
SDA45: J181.3, J182.3, J183.3, R272.1, U46.5
SDA46: J185.3, J186.3, J187.3, R278.1, U47.5
SDA47: J189.3, J190.3, J191.3, R284.1, U48.5
SDA48: J193.3, J194.3, J195.3, R290.1, U49.5
SDA49: J197.3, J198.3, J199.3, R296.1, U50.5
VDD: C4.1, R6.1, U2.10
VDD1: C2.1, R12.1, U1.10
VDD2: C5.1, R18.1, U3.10
VDD3: C7.1, R24.1, U4.10
VDD4: C9.1, R30.1, U5.10
VDD5: C11.1, R36.1, U6.10
VDD6: C13.1, R42.1, U7.10
VDD7: C15.1, R48.1, U8.10
VDD8: C17.1, R54.1, U9.10
VDD9: C19.1, R60.1, U10.10
VDD10: C21.1, R66.1, U11.10
VDD11: C23.1, R72.1, U12.10
VDD12: C25.1, R78.1, U13.10
VDD13: C27.1, R84.1, U14.10
VDD14: C29.1, R90.1, U15.10
VDD15: C31.1, R96.1, U16.10
VDD16: C33.1, R102.1, U17.10
VDD17: C35.1, R108.1, U18.10
VDD18: C37.1, R114.1, U19.10
VDD19: C39.1, R120.1, U20.10
VDD20: C41.1, R126.1, U21.10
VDD21: C43.1, R132.1, U22.10
VDD22: C45.1, R138.1, U23.10
VDD23: C47.1, R144.1, U24.10
VDD24: C49.1, R150.1, U25.10
VDD25: C51.1, R156.1, U26.10
VDD26: C53.1, R162.1, U27.10
VDD27: C55.1, R168.1, U28.10
VDD28: C57.1, R174.1, U29.10
VDD29: C59.1, R180.1, U30.10
VDD30: C61.1, R186.1, U31.10
VDD31: C63.1, R192.1, U32.10
VDD32: C65.1, R198.1, U33.10
VDD33: C67.1, R204.1, U34.10
VDD34: C69.1, R210.1, U35.10
VDD35: C71.1, R216.1, U36.10
VDD36: C73.1, R222.1, U37.10
VDD37: C75.1, R228.1, U38.10
VDD38: C77.1, R234.1, U39.10
VDD39: C79.1, R240.1, U40.10
VDD40: C81.1, R246.1, U41.10
VDD41: C83.1, R252.1, U42.10
VDD42: C85.1, R258.1, U43.10
VDD43: C87.1, R264.1, U44.10
VDD44: C89.1, R270.1, U45.10
VDD45: C91.1, R276.1, U46.10
VDD46: C93.1, R282.1, U47.10
VDD47: C95.1, R288.1, U48.10
VDD48: C97.1, R294.1, U49.10
VDD49: C99.1, R300.1, U50.10

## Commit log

2017-06-16 added eagle files
2017-06-19 Added .git ignore, readme, etc...
2017-06-20 Updated file structure to match SFE repo
2017-07-31 Changed sensor to AK9753
2017-08-14 Moved pins to fit Arduino I2C layout, fixed JP8 silk
2017-08-14 post design review changes
2017-08-15 added dimensions, post checklist changes
2017-08-15 Added standoffs to measures
2017-08-23 Moved engineering checklist
2017-08-28 Fixed that route out
2017-10-19 Pre Review commit
2017-10-20 design review checklist
2017-10-23 v10 fixes
2017-10-23 fixed trace
2017-10-25 Panel
2017-11-27 cleaned up repo, readme
2017-11-27 Squashed 'Libraries/Arduino/' content from commit d7ca767
    git-subtree-dir: Libraries/Arduino
    git-subtree-split: d7ca767f7c6202b82017d6734e0e1da681875f72
2017-11-27 ReAdded schematic
2018-01-18 Update README.md
    Update repository contents and link to hookup guide.
